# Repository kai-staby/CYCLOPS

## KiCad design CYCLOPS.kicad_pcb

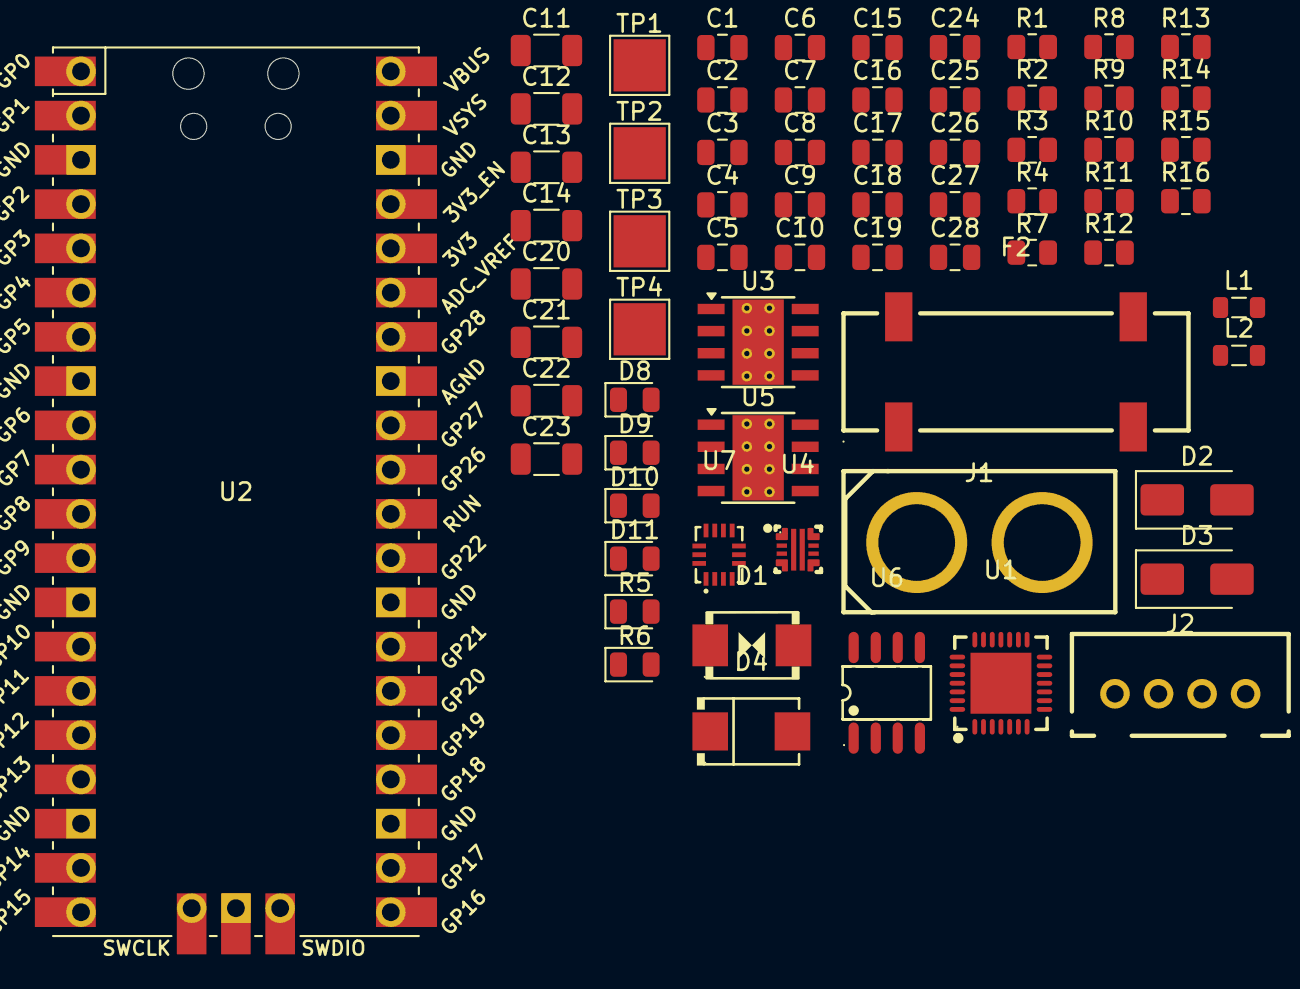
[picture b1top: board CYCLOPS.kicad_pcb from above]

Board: 2 copper layers, 68 parts (0 on the bottom side), 30 nets, no tracks yet.

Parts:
C1: 2.2nF; C_0805_2012Metric
C2: 1.2nF; C_0805_2012Metric
C3, C4, C10, C17: 1uF; C_0805_2012Metric
C5, C6, C16: 220nF; C_0805_2012Metric
C7, C15: 10uF; C_0805_2012Metric
C8, C18, C25, C27, C28: 100nF; C_0805_2012Metric
C9, C19: Open; C_0805_2012Metric
C11, C12, C13, C14, C20, C21, C22, C23: 22uF; C_1206_3216Metric
C24: 47uF; C_0805_2012Metric
C26: 100uF; C_0805_2012Metric
D1: SMBJ18CA; SMB_L4.6-W3.6-LS5.3-BI
D2, D3: SS14; D_SMA
D4: SMBJ17A; SMB_L4.6-W3.6-LS5.3-RD
D8, D9, D10, D11: LED_RED; LED_0805_2012Metric
F2: Fuse; FUSE-SMD_4P-L19.8-W6.7_3587-10
J1: XT60; CONN-TH_XT60
J2: B4B-XH-A; CONN-TH_B4B-XH-A-LF-SN
L1: 8uH; L_0805_2012Metric
L2: 15uH; L_0805_2012Metric
R1: 470k; R_0805_2012Metric
R2: 19.6k; R_0805_2012Metric
R3: 32.4k; R_0805_2012Metric
R4: 1.1k; R_0805_2012Metric
R5, R6: 10k; LED_0805_2012Metric
R7, R9, R11: 100k; R_0805_2012Metric
R8: 24.9k; R_0805_2012Metric
R10: 12.5k; R_0805_2012Metric
R12: 20k; R_0805_2012Metric
R13, R14: 7.5k; R_0805_2012Metric
R15: 1.5k; R_0805_2012Metric
R16: 3.6k; R_0805_2012Metric
TP1, TP2, TP3, TP4: TestPoint_Small; TestPoint_Pad_3.0x3.0mm
U1: TMC2209; QFN-28_L5.0-W5.0-P0.50-BL-EP
U2: RP2350 Pico 2; RPi_Pico_SMD_TH
U3, U5: LMR33630ADDA; Texas_HSOP-8-1EP_3.9x4.9mm_P1.27mm_ThermalVias
U4: TPS259470ARPWR; VQFN-10_L2.0-W2.0-P0.45-TL
U6: MLX90316KDC-BCG-000-RE; SOIC-8_L4.9-W3.9-P1.27-LS6.0-BL
U7: LSM6DSRXTR; LGA-14_L3.0-W2.5-P0.50-BL

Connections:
5V_REG: C9.1, C11.1, C12.1, C13.1, C14.1, D3.2 (A), L1.2, R7.1, R15.2, TP1.1 (1_1)
9V_REG: C19.1, C20.1, C21.1, C22.1, C23.1, L2.2, R9.1, R16.2, TP2.1 (1_1)
+3V3: R5.1, R6.1
/EFUSE_AUXOFF: R5.2, U4.3 (PG/AUXOFF)
/EFUSE_FLT: R6.2, U4.4 (~FLT/PGTH)
/VBAT_SENSE: C25.1, R11.2, R12.1
GND: C1.2, C2.2, C3.2, C4.2, C5.2, C6.2, C7.2, C10.2, C11.2, C12.2, C13.2, C14.2, C15.2, C16.2, C17.2, C20.2, C21.2, C22.2, C23.2, C24.2, C25.2, C28.2, D1.2 (A), D2.2 (A), D8.1 (K), D9.1 (K), D10.1 (K), D11.1 (K), J1.1 (-), R3.2, R4.2, R8.2, R10.2, R12.2, U2.3 (GND), U2.8 (GND), U2.13 (GND), U2.18 (GND), U2.38 (GND), U2.42 (GND), U3.1 (GND), U3.9 (GND), U4.8 (GND), U5.1 (GND), U5.9 (GND)
unnamed: C26.1, C27.1
unnamed: C26.2, C27.2
unnamed: C4.1, D1.1 (K), F2.2, R13.2, U4.5 (IN)
unnamed: C24.1, C28.1, D3.1 (K), U2.39 (VSYS)
unnamed: D8.2 (A), R13.1
unnamed: D9.2 (A), R14.1
unnamed: D10.2 (A), R15.1
unnamed: D11.2 (A), R16.1
unnamed: C8.1, U3.7 (BOOT)
unnamed: C9.2, R7.2, R8.1, U3.5 (FB)
unnamed: C8.2, L1.1, U3.8 (SW)
unnamed: C10.1, U3.6 (VCC)
unnamed: C2.1, U4.7 (DVDT)
unnamed: C5.1, R1.2, R2.1, U4.1 (EN/UVLO)
unnamed: R4.1, U4.9 (ILM)
unnamed: C1.1, U4.10 (ITIMER)
unnamed: R2.2, R3.1, U4.2 (OVLO/OVCSEL)
unnamed: C18.1, U5.7 (BOOT)
unnamed: C19.2, R9.2, R10.1, U5.5 (FB)
unnamed: C18.2, L2.1, U5.8 (SW)
unnamed: C17.1, U5.6 (VCC)
VBAT: F2.1, J1.2 (+), TP3.1 (1_1)
VBAT_PROT: C3.1, C6.1, C7.1, C15.1, C16.1, D2.1 (K), R11.1, R14.2, TP4.1 (1_1), U3.2 (VIN), U3.3 (EN), U4.6 (OUT), U5.2 (VIN), U5.3 (EN)
